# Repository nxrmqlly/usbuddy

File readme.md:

# usbuddy

A cute USB buddy. The PCB plugs straight into your laptop and can show messages based on serial input.
Powered by the `CH552G`, a generic `0.91" 128x32 SSD1305`, and a `WS2812B-2020` Neopixel.

## PCB

## CAD

### [OnShape Link](https://cad.onshape.com/documents/ad3ec215ff10d03571851e1e/w/97fc9671f557026641b18237/e/4b67f7499092e09124438d32)

## BOM

| Designator | Footprint                  | Quantity | Value               | LCSC Part # | Cost (1u) |
| ---------- | -------------------------- | -------- | ------------------- | ----------- | --------- |
| C1, C2     | 0603                       | 2        | 100n                | C14663      | $0.04     |
| D2         | 0805                       | 1        | KT-0805G            | C2297       | $0.02     |
| J1         | USB-A                      | 1        | USB_A               |             |           |
| R1         | 0603                       | 1        | 10k                 | C25804      | $0.01     |
| R2         | 0603                       | 1        | 1k                  | C21190      | $0.01     |
| SW1        | SW_SPST_TS-1088-xR020      | 1        | SW_Push             | C720477     | $0.05     |
| U1         | SOIC-16_3.9x9.9mm_P1.27mm  | 1        | CH552G              | C111292     | $0.74     |
| U2         | ER_OLEDM0.91_1x-I2C_NoCtyd | 1        | ER_OLEDM0.91_1x-I2C |             | $1.20     |

## Cost of Production

| Option                 | Qty | PCB Fabrication | PCBA & Parts | OLED + LED | Shipping |  **Total** |
| ---------------------- | --: | --------------: | -----------: | ---------: | -------: | ---------: |
| **5 assembled (ENIG)** |   5 |          $20.62 |       $18.03 |      $6.00 |    $9.92 | **$54.57** |
| **5 assembled (HASL)** |   5 |           $4.00 |       $18.03 |      $6.00 |    $9.92 | **$39.95** |

### Discounts (not accounted in total)

- -$2.00 JLCONE App
- -$9.00 PCBA Coupon

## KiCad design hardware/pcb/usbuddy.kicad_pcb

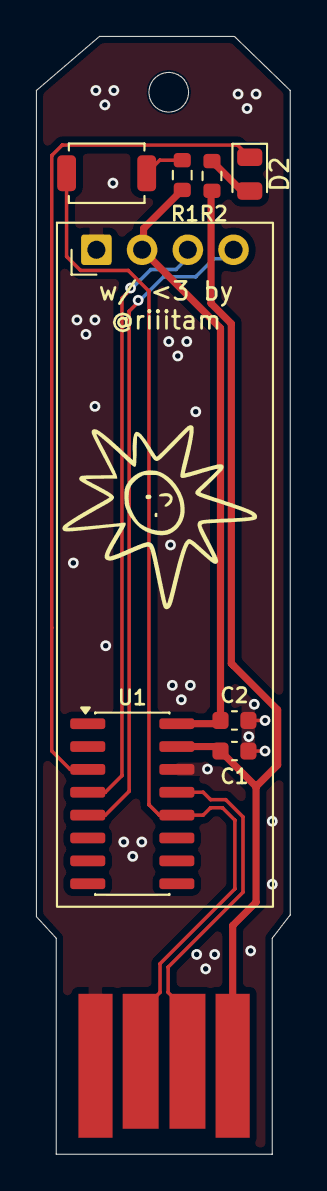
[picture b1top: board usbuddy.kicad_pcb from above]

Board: 2 copper layers, 14.1 x 62.1 mm, 10 parts (0 on the bottom side), 10 nets.

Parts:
C1, C2: 100n; C_0603_1608Metric
D2: KT-0805G; LED_0805_2012Metric
H1: MountingHole; MountingHole_2.2mm_M2
J1: USB_A; USB-A
R1: 10k; R_0603_1608Metric
R2: 1k; R_0603_1608Metric
SW1: SW_Push; SW_SPST_TS-1088-xR020
U1: CH552G; SOIC-16_3.9x9.9mm_P1.27mm
U2: ER_OLEDM0.91_1x-I2C; ER_OLEDM0.91_1x-I2C_NoCtyd

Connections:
+3V3: C2.1, R1.1, U1.16 (3V3), U2.2 (VCC)
D+: J1.3 (D+), SW1.1, U1.12 (P3.6)
D-: J1.2 (D-), U1.13 (P3.7)
GND: C1.2, C2.2, J1.4 (GND), U1.14 (GND), U2.1 (GND)
LED: D2.1 (K), U1.3 (P1.5)
unnamed: D2.2 (A), R2.2
unnamed: R1.2, SW1.2
SCL: U1.4 (P1.6), U2.3 (SCL)
SDA: U1.5 (P1.7), U2.4 (SDA)
VBUS: C1.1, J1.1 (VBUS), R2.1, U1.15 (VCC)
